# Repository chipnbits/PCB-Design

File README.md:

# PCB-Design

### Files:
- PCB Course Certificate : A certificate showing completion of 30 hour PCB design course
- overview.png : A visual overview of the project and results
- pcbDesign.kicad_pcb : PCB layout file in KiCAD
- signalGeneratorGerber.zip : Gerber files

### Description:

A signal generator PCB design project performed as part of a 30 hour course through the UBC PHAS Elab, Fall 2022.  A 15V DC signal is passed through a voltage regulator to produce 5V DC.  The 5V is passed through a 5V -> -5V converter to power the rails of an op-amp that can control output signal amplitude.  5V powers a 100kHz Timer/Oscillator that produces a squarewave signal that can be tuned in combination with the potentiometers and the op-amp.  Tuned signal can be read from a through-hole test port.

Project phases included:

#### Design
- Creating a schematic in EDA software (KiCad), including additions to the parts library.
- Creating custom component footprints to match manufacturer specifications.
- Review of good design priciples for PCB circuit layout.
- Manual layout of circuit onto a two-layer PCB, design rules specifications, variable width traces.
- Custom silk screen layering, sizing, and drill holes for ease of assembly.
- Gerber file production and PCB ordering.

#### Assembly
- Manual soldering of surface mount components with a Sainsmart TS-100 Iron.
- Testing and validation with digital oscilloscope and multimeter.
- Use of one jumper wire to correct a connection issue not flagged properly by EDA.

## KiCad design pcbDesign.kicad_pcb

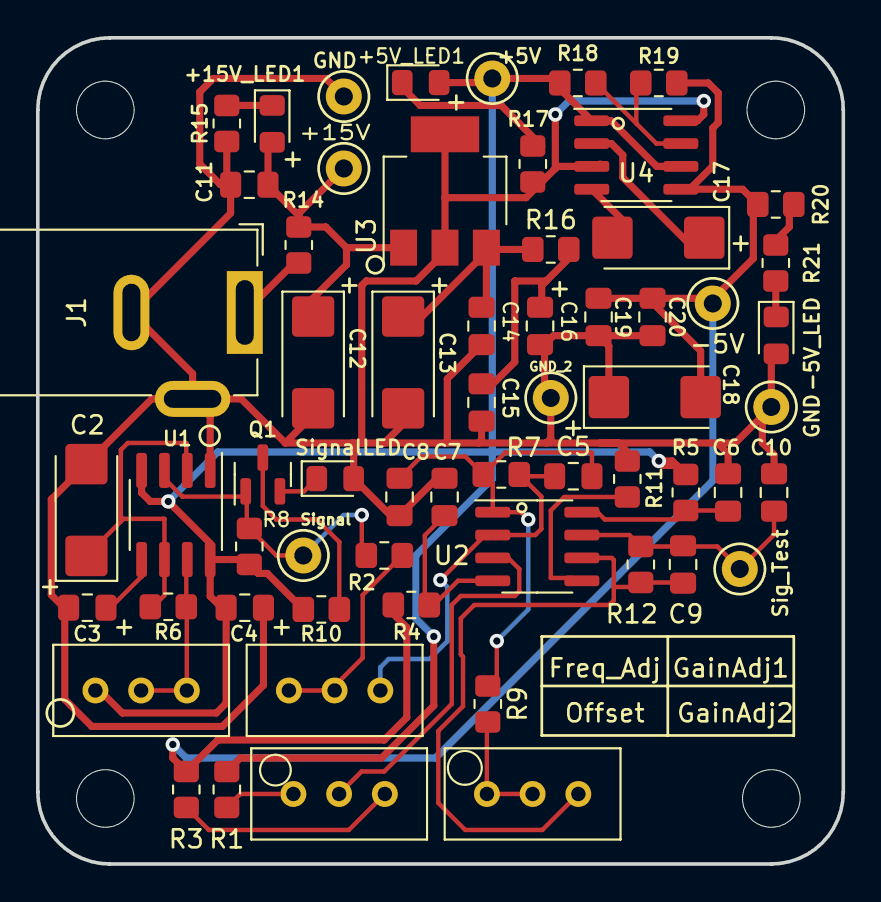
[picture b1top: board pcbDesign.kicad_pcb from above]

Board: 2 copper layers, 44.7 x 45.9 mm, 65 parts (0 on the bottom side), 30 nets.

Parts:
+5V, +15V: TestPoint; TestPoint_Keystone_5000-5004_Miniature
+5V_LED1, +15V_LED1: LED
-5V: TestPoint; TestPoint_Keystone_5000-5004_Miniature
-5V_LED: LED
C2, C12, C13, C17, C18: 10u; polar capacitor
C3, C4, C6, C7, C10, C11, C14, C15, C19, C20: 10n; C 0805
C5, C9: 22p; C 0805
C8: DNP; C 0805
C16: 10u; C 0805
Freq_Adj: 100K; Potentiometer_Bourns_3296W_Vertical
GND: TestPoint; TestPoint_Keystone_5000-5004_Miniature
GND#2: TestPoint; TestPoint_Keystone_5000-5004_Miniature
GND_2: TestPoint; TestPoint_Keystone_5000-5004_Miniature
GainAdj1, GainAdj2: 100K; Potentiometer_Bourns_3296W_Vertical
H1: MountingHole; MountingHole_3.2mm_M3
H2, H3, H4: MountingHole; MountingHole_3.2mm_M3_DIN965
J1: Barrel_Jack_Switch; BarrelJack_GCT_DCJ200-10-A_Horizontal
Offset: 100K; Potentiometer_Bourns_3296W_Vertical
Q1: DMN10H700S; SOT-23
R1, R2, R3, R9: 1K; R_0805_2012Metric_Pad1.20x1.40mm_HandSolder
R4, R5: 1R; R_0805_2012Metric_Pad1.20x1.40mm_HandSolder
R6, R7, R12: 10K; R_0805_2012Metric_Pad1.20x1.40mm_HandSolder
R8: 100R; R_0805_2012Metric_Pad1.20x1.40mm_HandSolder
R10, R17, R21: 150R; R_0805_2012Metric_Pad1.20x1.40mm_HandSolder
R11: 25; R_0805_2012Metric_Pad1.20x1.40mm_HandSolder
R14, R16, R20: 0R; R_0805_2012Metric_Pad1.20x1.40mm_HandSolder
R15: 650R; R_0805_2012Metric_Pad1.20x1.40mm_HandSolder
R18, R19: 100K; R_0805_2012Metric_Pad1.20x1.40mm_HandSolder
Sig_Test: TestPoint; TestPoint_Keystone_5000-5004_Miniature
Signal: TestPoint; TestPoint_Keystone_5000-5004_Miniature
SignalLED: LED
U1: NE555P; NE555DR
U2: AD8039; SOIC-8_3.9x4.9mm_P1.27mm
U3: LM7805MPX; LM7805
U4: MAX889; SOIC-8_3.9x4.9mm_P1.27mm

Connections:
5V: +5V.1, +5V_LED1.2 (A), C4.2, C15.1, C16.1, Freq_Adj.1, R1.1, R5.1, R8.1, R10.2, R16.2, R18.1, U1.4 (R), U1.8 (VCC), U4.1 (IN), U4.6 (/SHDN)
-5V: -5V.1, C18.2, C19.1, C20.1, R3.2, R4.1, R19.2, R20.1, R20.2, R21.1, U4.5 (OUT)
/PS/+5V: C13.1, C14.1, R16.1, U3.3 (VO)
/PS/+15V: J1.1, R14.1
GND: -5V_LED.2 (A), C2.2, C3.2, C4.1, C6.2, C7.2, C8.1, C10.1, C11.2, C12.2, C13.2, C14.2, C15.2, C16.2, C18.1, C19.2, C20.2, GND.1, GND#2.1, GND_2.1, J1.2, J1.3, R11.1, R15.2, R17.2, SignalLED.2 (A), U1.1 (GND), U3.2 (GND), U4.3 (GDN), U4.8 (AGDN)
unnamed: +5V_LED1.1 (K), R17.1
unnamed: +15V.1, +15V_LED1.2 (A), C11.1, C12.1, R14.2, U3.1 (VI)
unnamed: +15V_LED1.1 (K), R15.1
unnamed: -5V_LED.1 (K), R21.2
unnamed: C2.1, R6.2, U1.2 (TR), U1.6 (THR)
unnamed: C3.1, U1.5 (CV)
unnamed: C5.1, GainAdj1.3, R7.1, U2.2 (IN-)
unnamed: C5.2, C8.2, R7.2, R9.1, U2.1 (OUT)
unnamed: C6.1, R5.2, U2.8 (V+)
unnamed: C7.1, R4.2, U2.4 (V-)
unnamed: C9.1, GainAdj2.3, R12.1, U2.6 (IN-)
unnamed: C9.2, C10.2, R12.2, Sig_Test.1, U2.7 (OUT)
unnamed: C17.1, U4.2 (CAP+)
unnamed: C17.2, U4.4 (CAP-)
unnamed: Freq_Adj.2, Freq_Adj.3, R6.1, U1.7 (DIS)
unnamed: GainAdj1.1, GainAdj1.2, R2.2
unnamed: GainAdj2.1, GainAdj2.2, R9.2
unnamed: Offset.1, R1.2
unnamed: Offset.2, U2.3 (IN+)
unnamed: Offset.3, R3.1
unnamed: Q1.2 (S), SignalLED.1 (K)
unnamed: Q1.3 (D), R10.1
unnamed: R11.2, U2.5 (IN+)
unnamed: R18.2, R19.1, U4.7 (FB)
Signal1: Q1.1 (G), R2.1, R8.2, Signal.1, U1.3 (Q)

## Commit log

2022-12-26 Gerber Files
